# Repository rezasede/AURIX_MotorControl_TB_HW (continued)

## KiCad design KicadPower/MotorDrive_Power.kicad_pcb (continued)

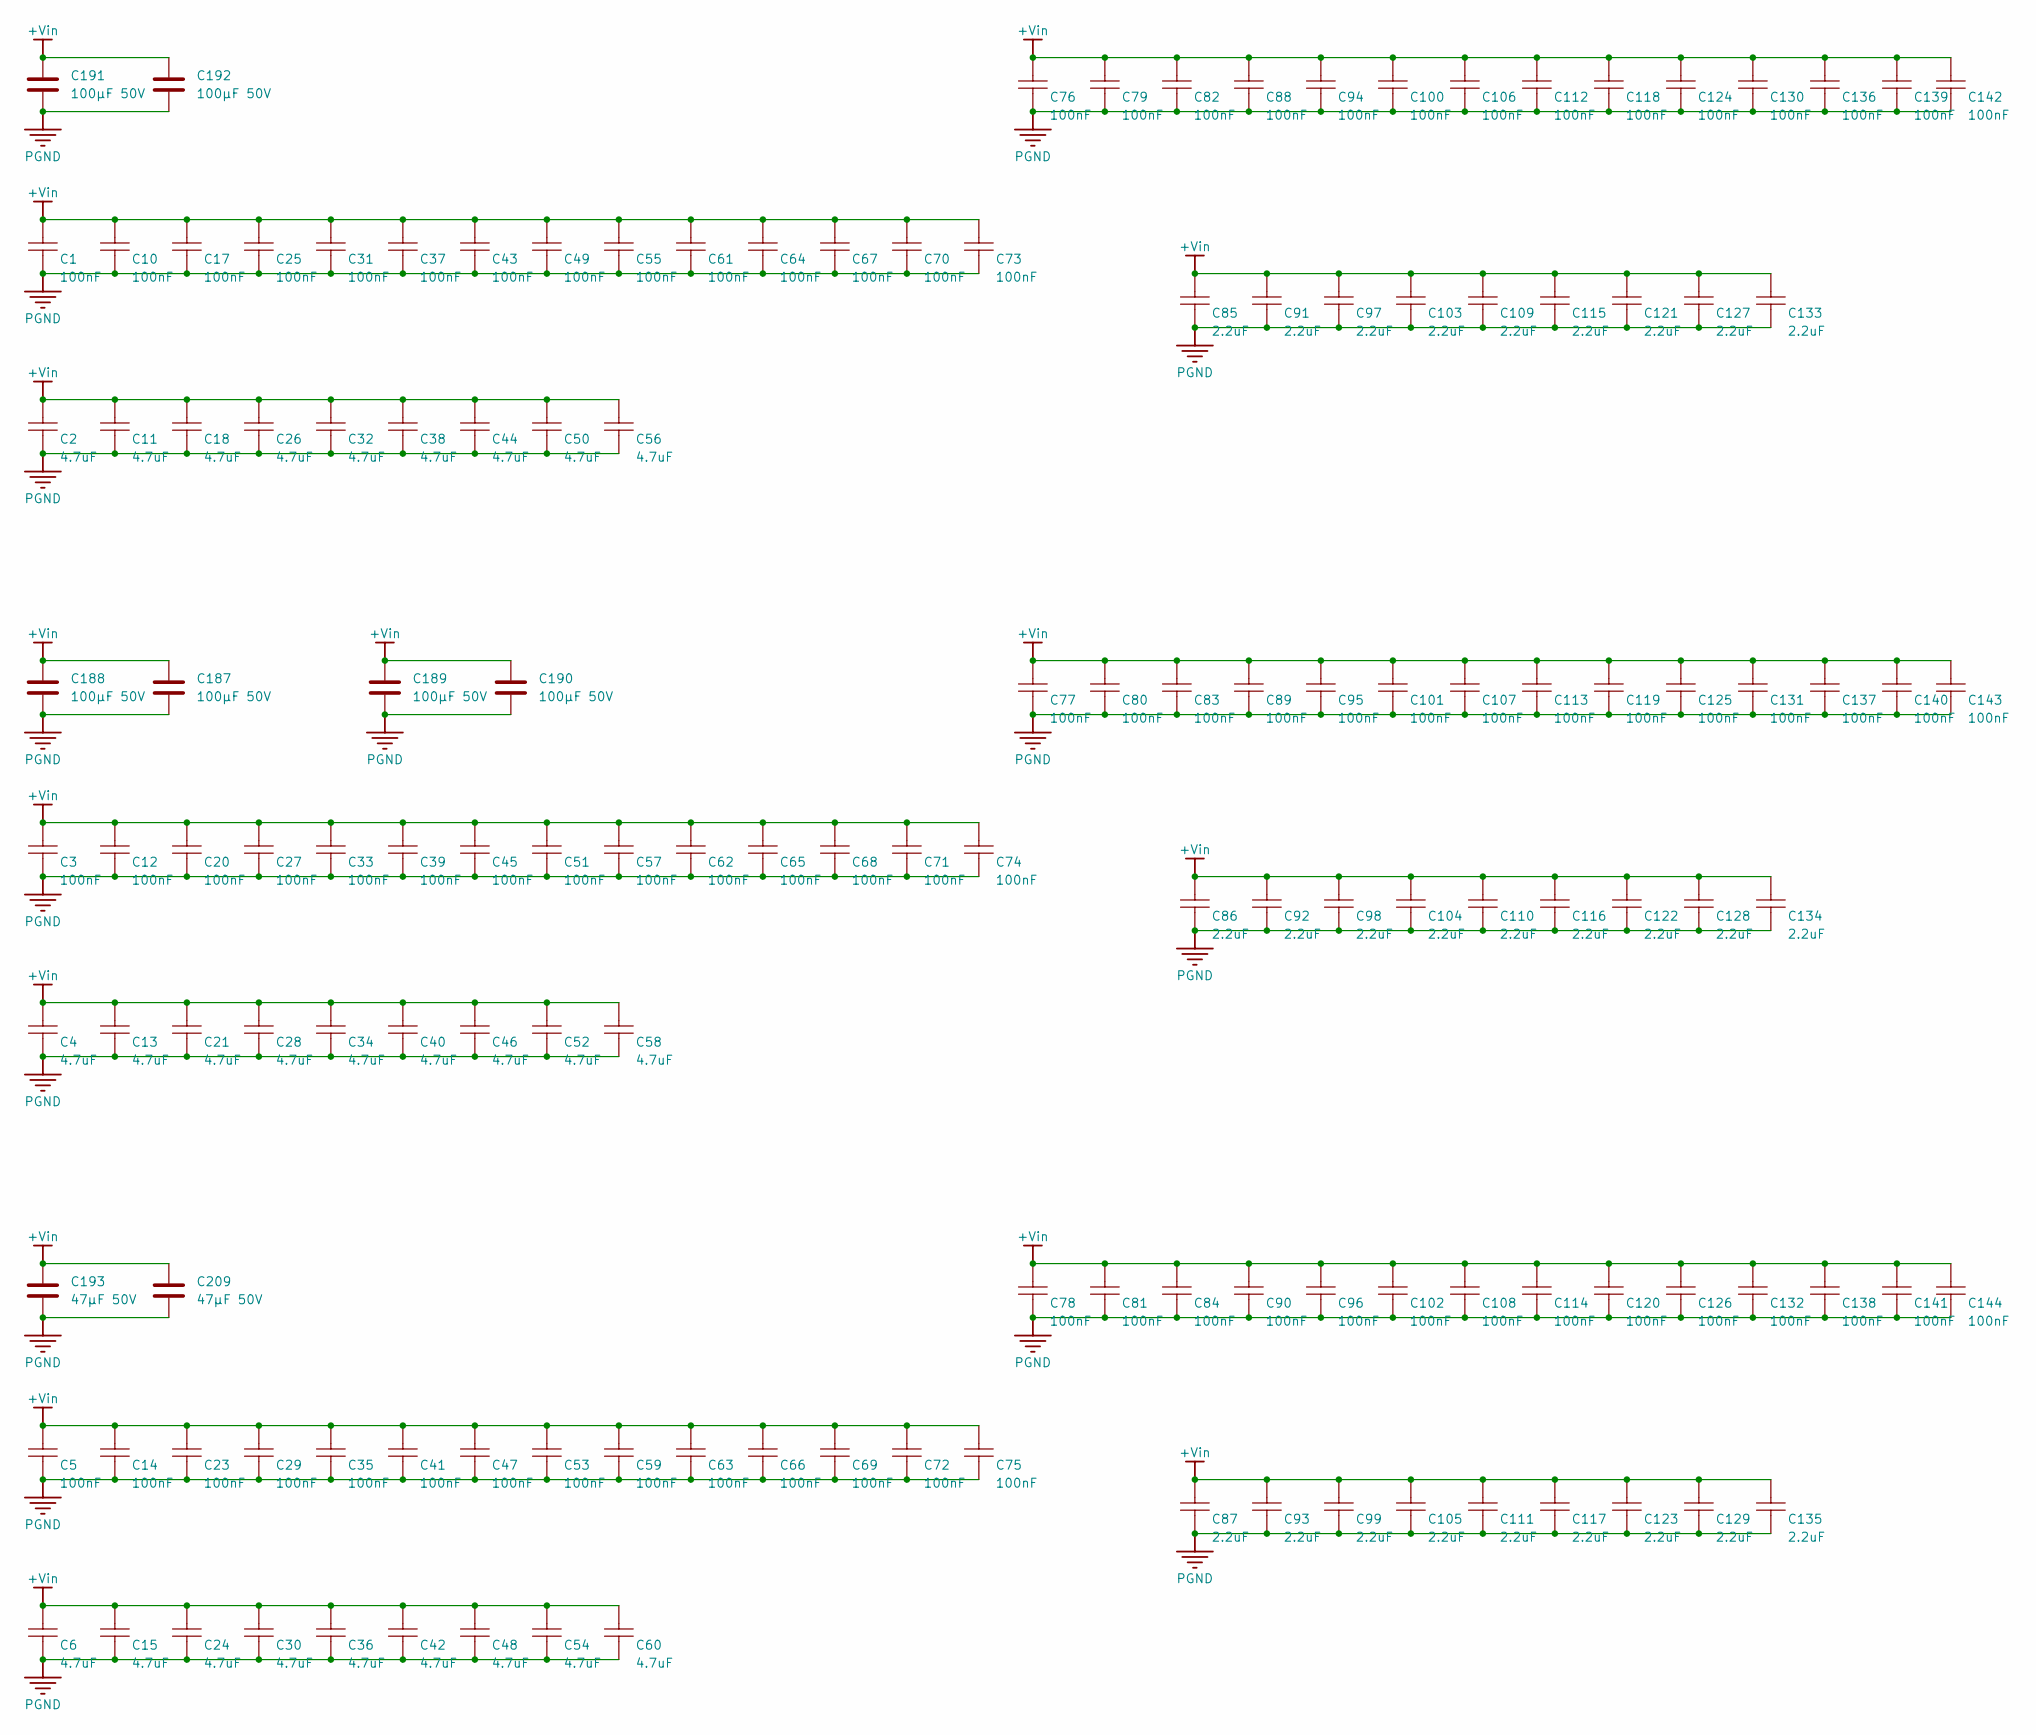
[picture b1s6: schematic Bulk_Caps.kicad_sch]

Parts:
C1, C3, C5, C10, C12, C14, C17, C20, C23, C25, C27, C29, C31, C33, C35, C37, C39, C41, C43, C45, C47, C49, C51, C53, C55, C57, C59, C61, C62, C63, C64, C65, C66, C67, C68, C69, C70, C71, C72, C73, C74, C75, C76, C77, C78, C79, C80, C81, C82, C83, C84, C88, C89, C90, C94, C95, C96, C100, C101, C102, C106, C107, C108, C112, C113, C114, C118, C119, C120, C124, C125, C126, C130, C131, C132, C136, C137, C138, C139, C140, C141, C142, C143, C144: Cap SMD; CAPC3216X100N
C2, C4, C6, C11, C13, C15, C18, C21, C24, C26, C28, C30, C32, C34, C36, C38, C40, C42, C44, C46, C48, C50, C52, C54, C56, C58, C60, C85, C86, C87, C91, C92, C93, C97, C98, C99, C103, C104, C105, C109, C110, C111, C115, C116, C117, C121, C122, C123, C127, C128, C129, C133, C134, C135: Cap SMD; CAPC3225X220N
C187, C188, C189, C190, C191, C192: 100µF 50V; C_Elec_8x10.2
C193, C209: 47µF 50V; C_Elec_6.3x7.7

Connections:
+Vin: C1.2, C2.2, C3.2, C4.2, C5.2, C6.2, C10.2, C11.2, C12.2, C13.2, C14.2, C15.2, C17.2, C18.2, C20.2, C21.2, C23.2, C24.2, C25.2, C26.2, C27.2, C28.2, C29.2, C30.2, C31.2, C32.2, C33.2, C34.2, C35.2, C36.2, C37.2, C38.2, C39.2, C40.2, C41.2, C42.2, C43.2, C44.2, C45.2, C46.2, C47.2, C48.2, C49.2, C50.2, C51.2, C52.2, C53.2, C54.2, C55.2, C56.2, C57.2, C58.2, C59.2, C60.2, C61.2, C62.2, C63.2, C64.2, C65.2, C66.2, C67.2, C68.2, C69.2, C70.2, C71.2, C72.2, C73.2, C74.2, C75.2, C76.2, C77.2, C78.2, C79.2, C80.2, C81.2, C82.2, C83.2, C84.2, C85.2, C86.2, C87.2, C88.2, C89.2, C90.2, C91.2, C92.2, C93.2, C94.2, C95.2, C96.2, C97.2, C98.2, C99.2, C100.2, C101.2, C102.2, C103.2, C104.2, C105.2, C106.2, C107.2, C108.2, C109.2, C110.2, C111.2, C112.2, C113.2, C114.2, C115.2, C116.2, C117.2, C118.2, C119.2, C120.2, C121.2, C122.2, C123.2, C124.2, C125.2, C126.2, C127.2, C128.2, C129.2, C130.2, C131.2, C132.2, C133.2, C134.2, C135.2, C136.2, C137.2, C138.2, C139.2, C140.2, C141.2, C142.2, C143.2, C144.2, C187.1, C188.1, C189.1, C190.1, C191.1, C192.1, C193.1, C209.1; also elsewhere on the board
PGND: C1.1, C2.1, C3.1, C4.1, C5.1, C6.1, C10.1, C11.1, C12.1, C13.1, C14.1, C15.1, C17.1, C18.1, C20.1, C21.1, C23.1, C24.1, C25.1, C26.1, C27.1, C28.1, C29.1, C30.1, C31.1, C32.1, C33.1, C34.1, C35.1, C36.1, C37.1, C38.1, C39.1, C40.1, C41.1, C42.1, C43.1, C44.1, C45.1, C46.1, C47.1, C48.1, C49.1, C50.1, C51.1, C52.1, C53.1, C54.1, C55.1, C56.1, C57.1, C58.1, C59.1, C60.1, C61.1, C62.1, C63.1, C64.1, C65.1, C66.1, C67.1, C68.1, C69.1, C70.1, C71.1, C72.1, C73.1, C74.1, C75.1, C76.1, C77.1, C78.1, C79.1, C80.1, C81.1, C82.1, C83.1, C84.1, C85.1, C86.1, C87.1, C88.1, C89.1, C90.1, C91.1, C92.1, C93.1, C94.1, C95.1, C96.1, C97.1, C98.1, C99.1, C100.1, C101.1, C102.1, C103.1, C104.1, C105.1, C106.1, C107.1, C108.1, C109.1, C110.1, C111.1, C112.1, C113.1, C114.1, C115.1, C116.1, C117.1, C118.1, C119.1, C120.1, C121.1, C122.1, C123.1, C124.1, C125.1, C126.1, C127.1, C128.1, C129.1, C130.1, C131.1, C132.1, C133.1, C134.1, C135.1, C136.1, C137.1, C138.1, C139.1, C140.1, C141.1, C142.1, C143.1, C144.1, C187.2, C188.2, C189.2, C190.2, C191.2, C192.2, C193.2, C209.2; also elsewhere on the board

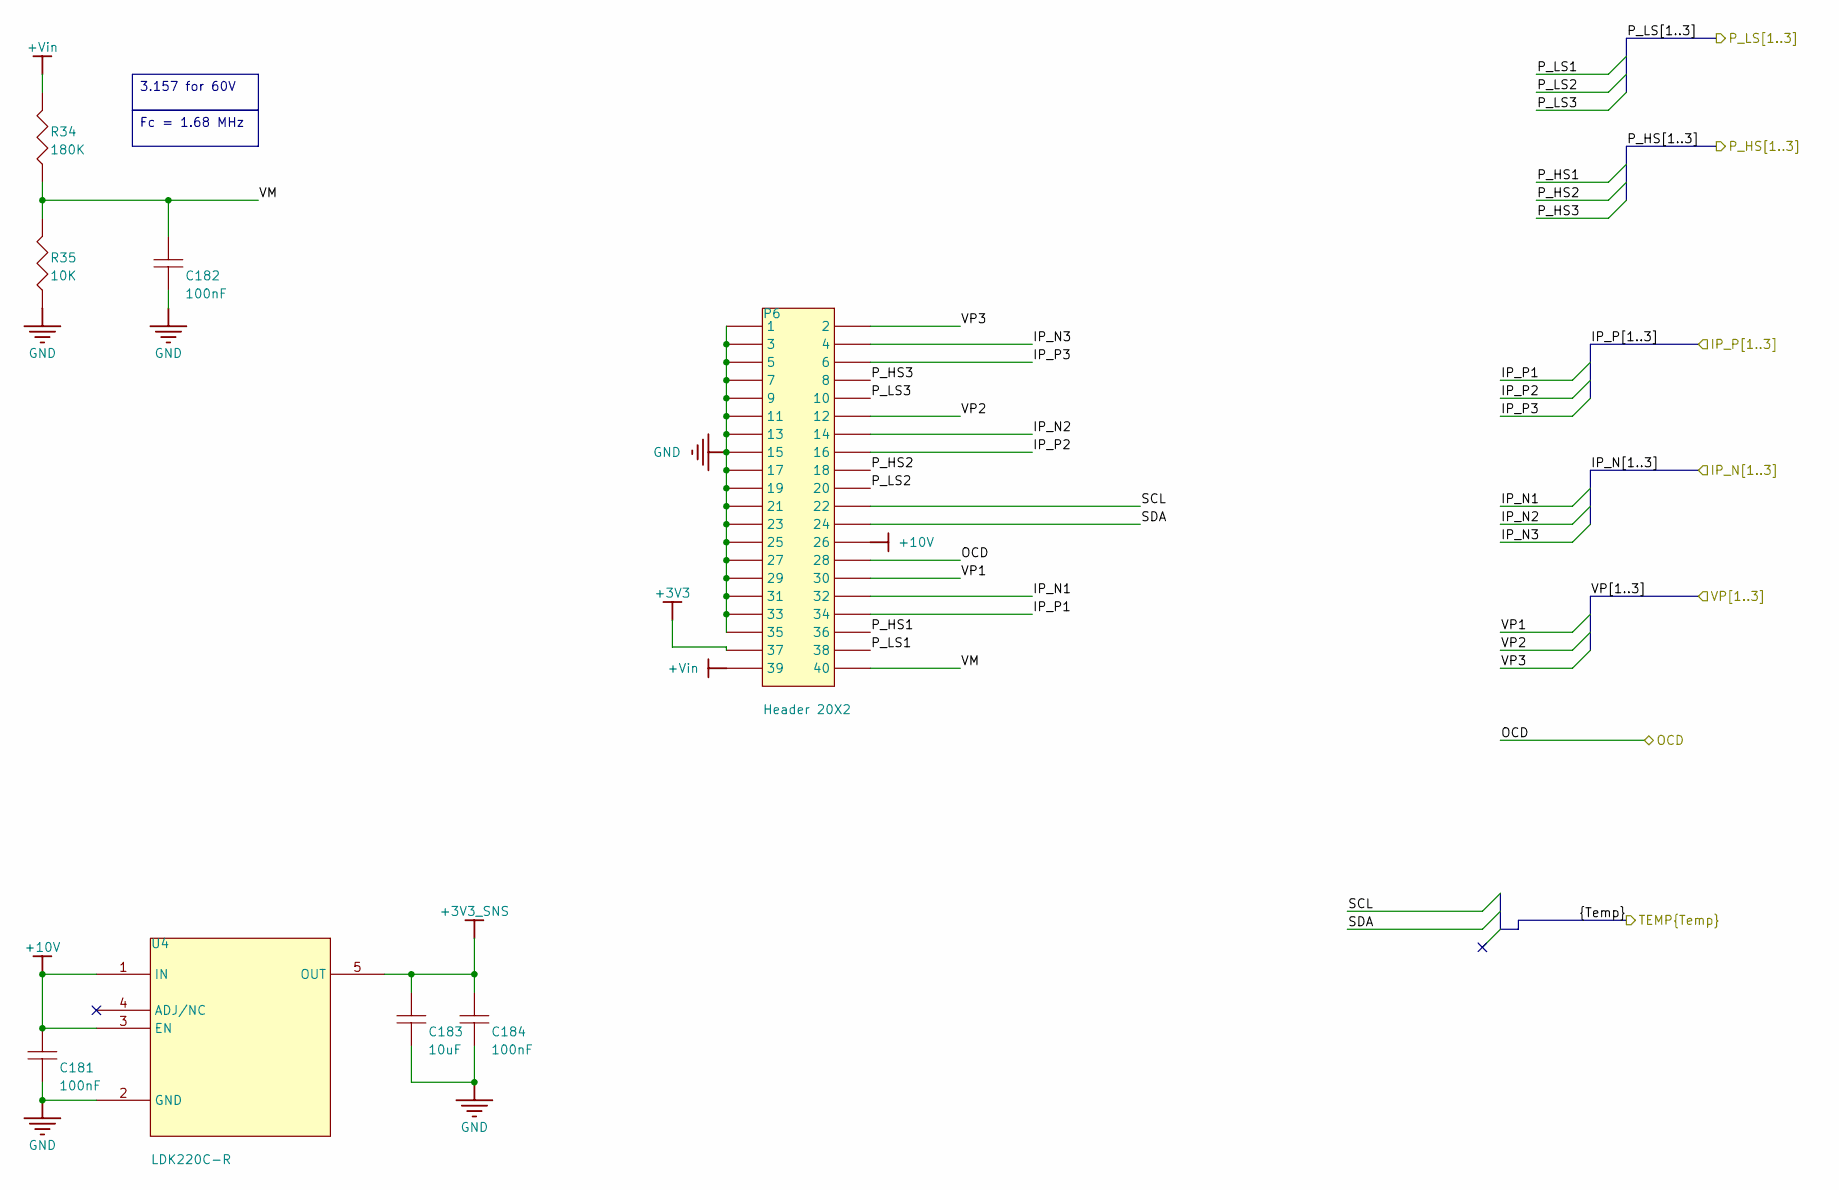
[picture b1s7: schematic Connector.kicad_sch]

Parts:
C181, C182, C183, C184: Cap SMD; CAPC1608X90N
P6: Header 20X2; HDR2X20-MD
R34, R35: Res SMD; RESC1608X55N
U4: LDK220C-R; SOT_220M-R_STM; MANUFACTURER_PART_NUMBER LDK220C-R

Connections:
+3V3: P6.37; also elsewhere on the board
+3V3_SNS: C183.2, C184.2, U4.5 (OUT); also elsewhere on the board
+10V: C181.2, P6.26, U4.1 (IN), U4.3 (EN); also elsewhere on the board
+Vin: P6.39, R34.2; also elsewhere on the board
/IP_N1: P6.32; also elsewhere on the board
/IP_N2: P6.14; also elsewhere on the board
/IP_N3: P6.4; also elsewhere on the board
/IP_P1: P6.34; also elsewhere on the board
/IP_P2: P6.16; also elsewhere on the board
/IP_P3: P6.6; also elsewhere on the board
/OCD: P6.28; also elsewhere on the board
/P_HS1: P6.36; also elsewhere on the board
/P_HS2: P6.18; also elsewhere on the board
/P_HS3: P6.8; also elsewhere on the board
/P_LS1: P6.38; also elsewhere on the board
/P_LS2: P6.20; also elsewhere on the board
/P_LS3: P6.10; also elsewhere on the board
/U_Connector/SCL: P6.22; also elsewhere on the board
/U_Connector/SDA: P6.24; also elsewhere on the board
/U_Connector/VM: C182.2, P6.40, R34.1, R35.2
/VP1: P6.30; also elsewhere on the board
/VP2: P6.12; also elsewhere on the board
/VP3: P6.2; also elsewhere on the board
GND: C181.1, C182.1, C183.1, C184.1, P6.1, P6.3, P6.5, P6.7, P6.9, P6.11, P6.13, P6.15, P6.17, P6.19, P6.21, P6.23, P6.25, P6.27, P6.29, P6.31, P6.33, P6.35, R35.1, U4.2 (GND); also elsewhere on the board

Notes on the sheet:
3.157 for 60V
Fc = 1.68 MHz

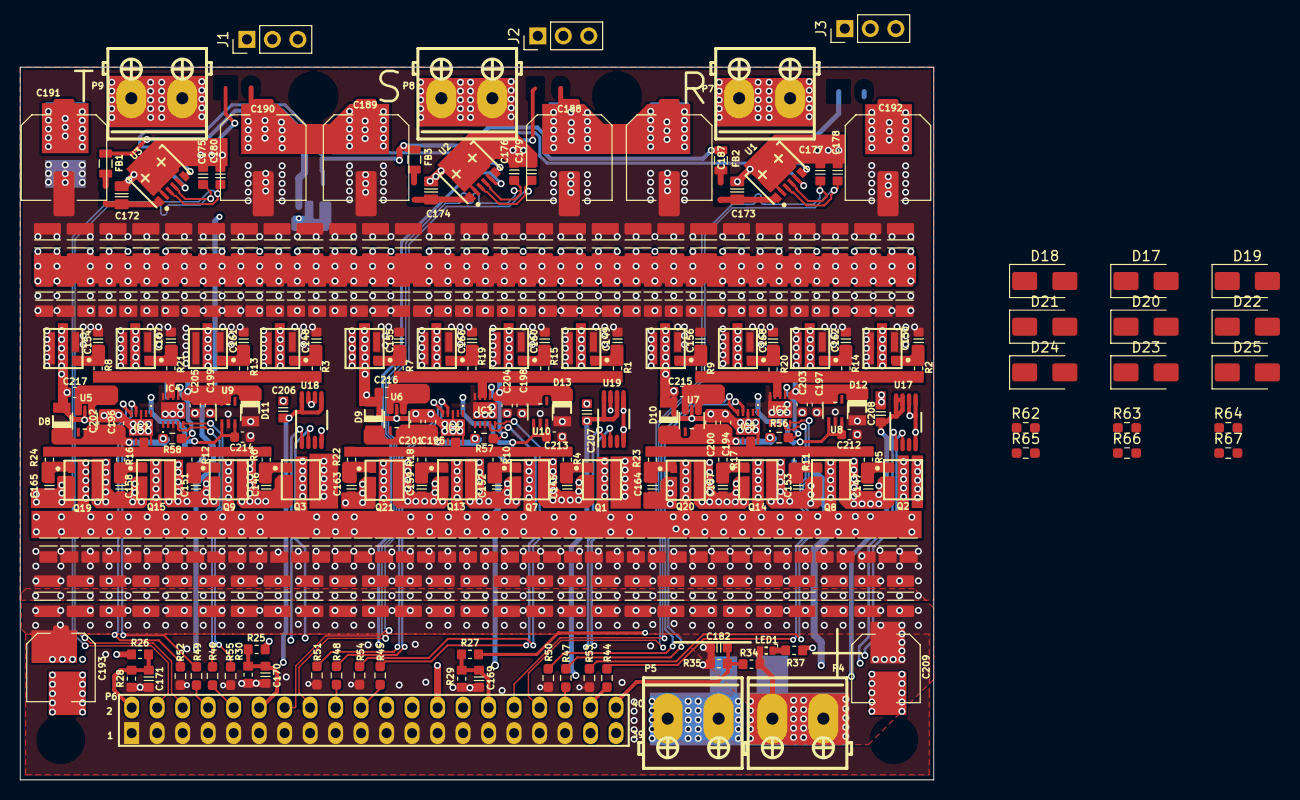
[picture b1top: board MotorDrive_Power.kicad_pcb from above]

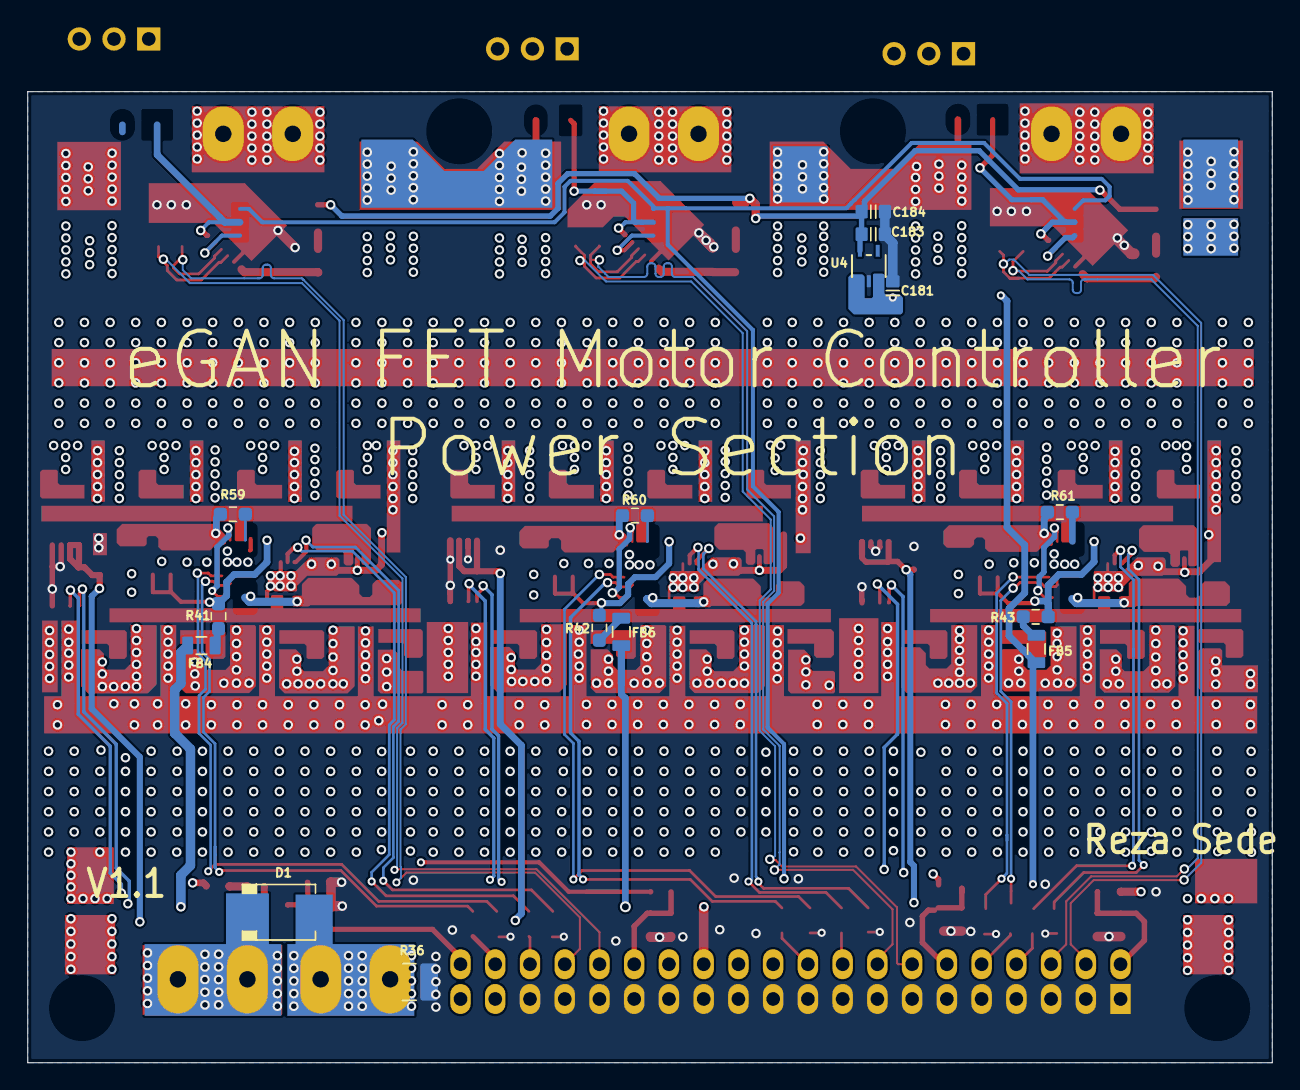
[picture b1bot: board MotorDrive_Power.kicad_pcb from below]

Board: 6 copper layers, 91.0 x 71.0 mm, 343 parts (15 on the bottom side), 104 nets.

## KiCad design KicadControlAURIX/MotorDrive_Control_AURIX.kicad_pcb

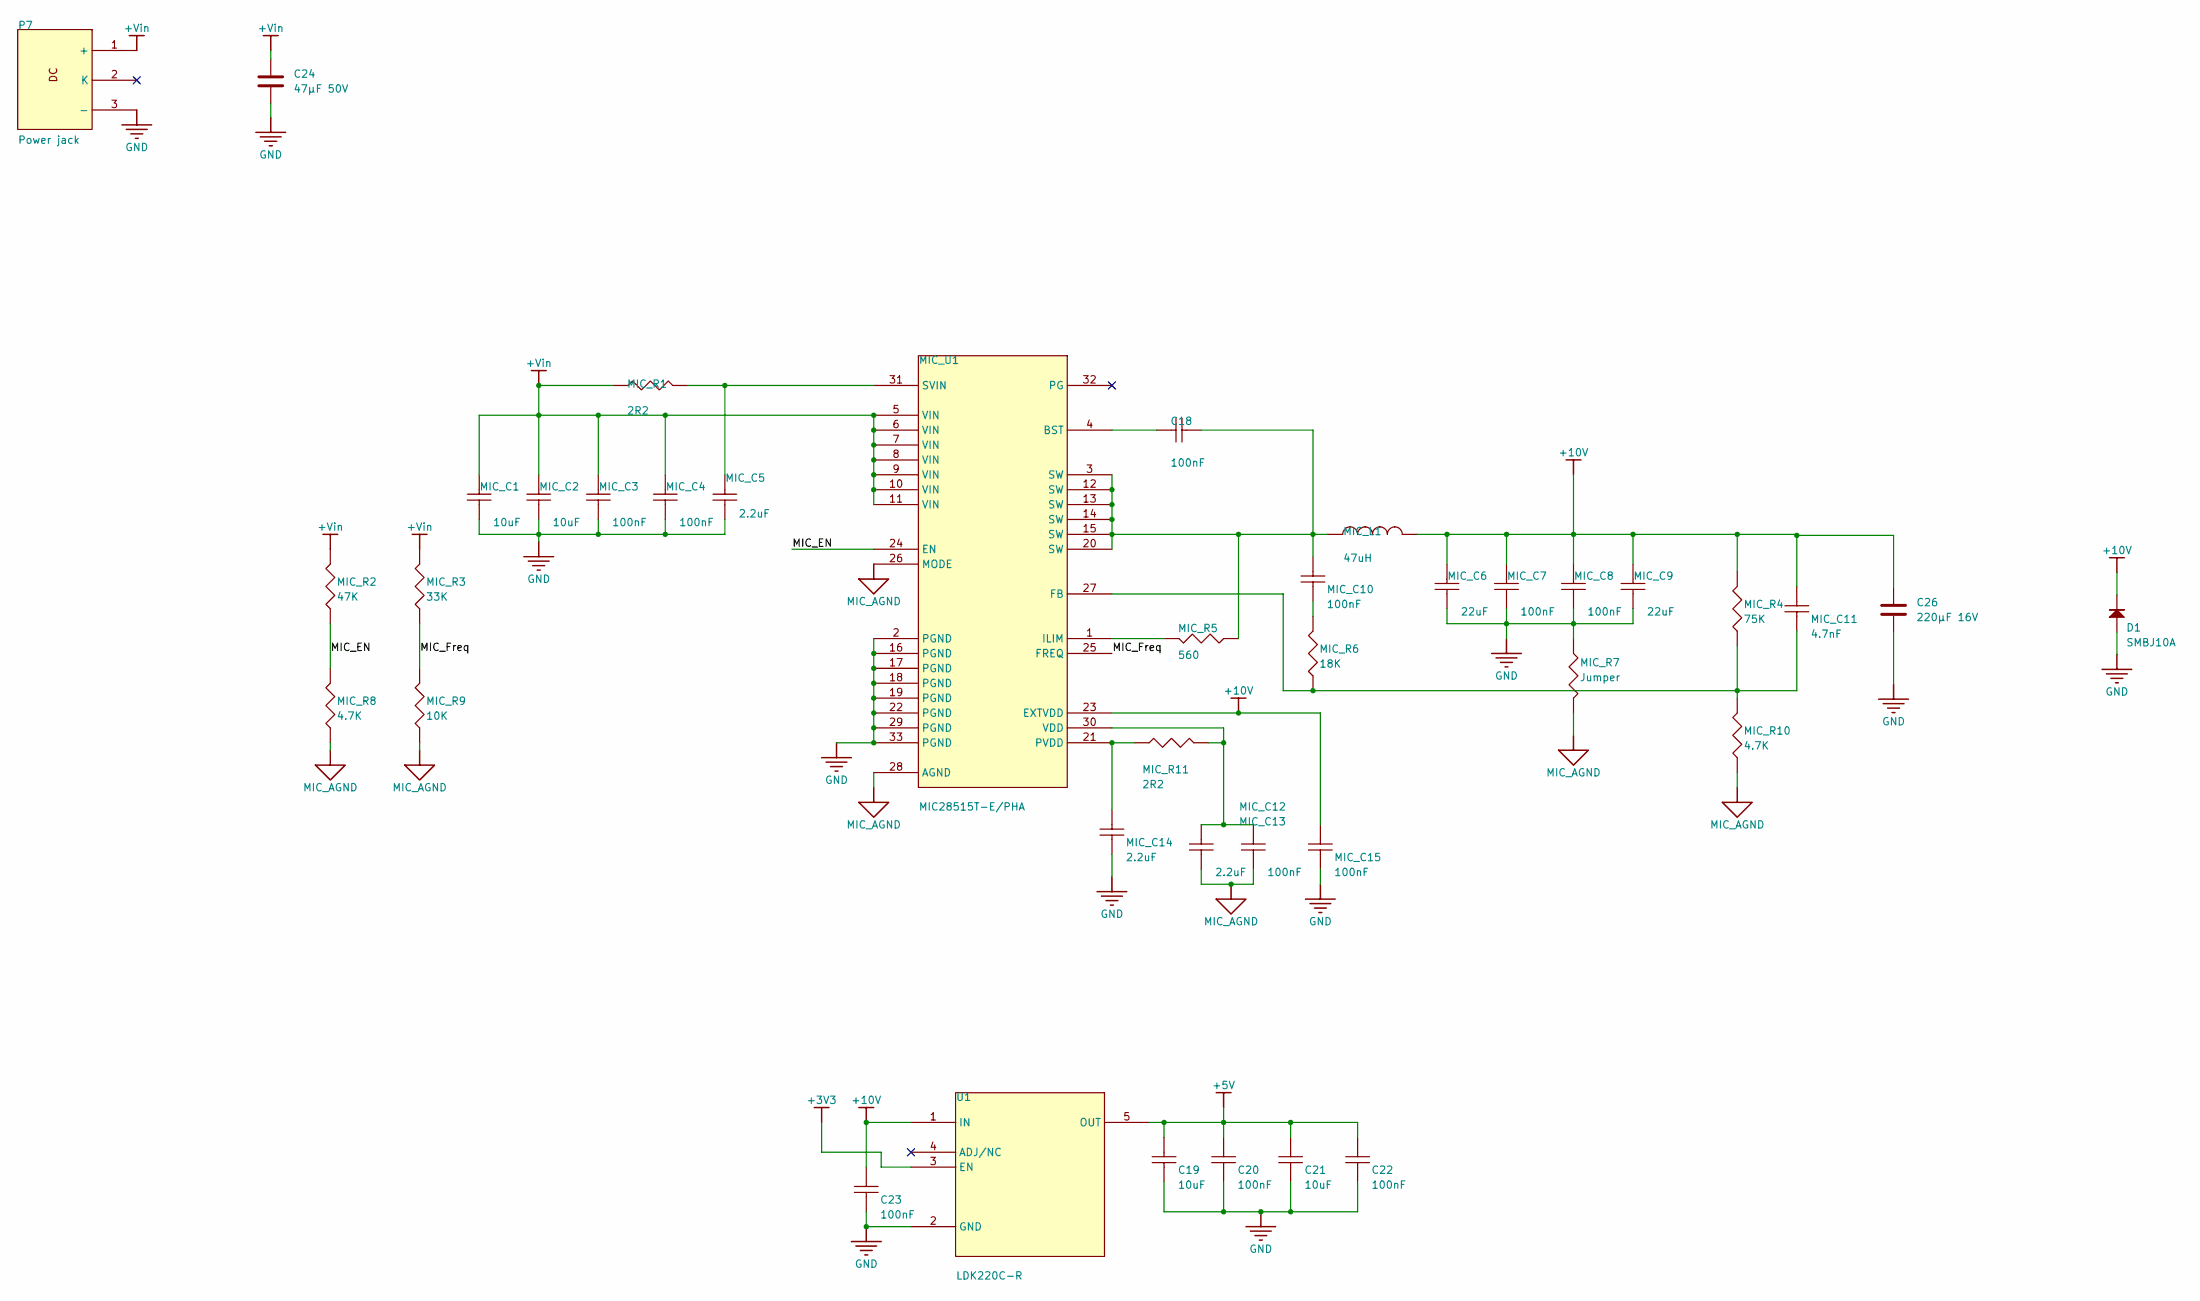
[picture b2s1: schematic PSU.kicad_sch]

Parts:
C18, C20, C22, C23: Cap SMD; CAPC1608X90N
C19, C21: Cap SMD; CAPC2012X135N
C24: 47µF 50V; C_Elec_6.3x7.7
C26: 220µF 16V; C_Elec_6.3x7.7
D1: SMBJ10A; DO-214AA
MIC_C1, MIC_C2, MIC_C5, MIC_C6, MIC_C9, MIC_C12, MIC_C14: Cap SMD; CAPC3216X100N
MIC_C3, MIC_C4, MIC_C13, MIC_C15: Cap SMD; CAPC2012X135N
MIC_C7, MIC_C8, MIC_C10, MIC_C11: Cap SMD; CAPC1608X90N
MIC_L1: Inductor; SCD503T-101K-N
MIC_R1, MIC_R2, MIC_R3, MIC_R4, MIC_R5, MIC_R6, MIC_R7, MIC_R8, MIC_R9, MIC_R10, MIC_R11: Res SMD; RESC1608X55N
MIC_U1: MIC28515T-E/PHA; VQFN32_PHA_MCH-M
P7: Power jack; power jaCK
U1: LDK220C-R; SOT_220M-R_STM; MANUFACTURER_PART_NUMBER LDK220C-R

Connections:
+3V3: U1.3 (EN); also elsewhere on the board
+5V: C19.2, C20.2, C21.2, C22.2, U1.5 (OUT); also elsewhere on the board
+10V: C23.2, C26.1, D1.K (2), MIC_C6.2, MIC_C7.2, MIC_C8.2, MIC_C9.2, MIC_C11.2, MIC_C15.2, MIC_L1.2, MIC_R4.2, MIC_U1.23 (EXTVDD), U1.1 (IN); also elsewhere on the board
+Vin: C24.1, MIC_C1.2, MIC_C2.2, MIC_C3.2, MIC_C4.2, MIC_R1.1, MIC_R2.2, MIC_R3.2, MIC_U1.5 (VIN), MIC_U1.6 (VIN), MIC_U1.7 (VIN), MIC_U1.8 (VIN), MIC_U1.9 (VIN), MIC_U1.10 (VIN), MIC_U1.11 (VIN), P7.1 (+); also elsewhere on the board
/U_PSU/MIC_EN: MIC_R2.1, MIC_R8.2, MIC_U1.24 (EN)
/U_PSU/MIC_Freq: MIC_R3.1, MIC_R9.2, MIC_U1.25 (FREQ)
GND: C19.1, C20.1, C21.1, C22.1, C23.1, C24.2, C26.2, D1.A (1), MIC_C1.1, MIC_C2.1, MIC_C3.1, MIC_C4.1, MIC_C5.2, MIC_C6.1, MIC_C7.1, MIC_C8.1, MIC_C9.1, MIC_C14.1, MIC_C15.1, MIC_R7.1, MIC_U1.2 (PGND), MIC_U1.16 (PGND), MIC_U1.17 (PGND), MIC_U1.18 (PGND), MIC_U1.19 (PGND), MIC_U1.22 (PGND), MIC_U1.29 (PGND), MIC_U1.33 (PGND), P7.3 (-), U1.2 (GND); also elsewhere on the board
MIC_AGND: MIC_C12.1, MIC_C13.1, MIC_R7.2, MIC_R8.1, MIC_R9.1, MIC_R10.1, MIC_U1.26 (MODE), MIC_U1.28 (AGND)
unnamed: C18.2, MIC_C10.2, MIC_L1.1, MIC_R5.1, MIC_U1.3 (SW), MIC_U1.12 (SW), MIC_U1.13 (SW), MIC_U1.14 (SW), MIC_U1.15 (SW), MIC_U1.20 (SW)
unnamed: MIC_C10.1, MIC_R6.2
unnamed: C18.1, MIC_U1.4 (BST)
unnamed: MIC_C11.1, MIC_R4.1, MIC_R6.1, MIC_R10.2, MIC_U1.27 (FB)
unnamed: MIC_R5.2, MIC_U1.1 (ILIM)
unnamed: MIC_C14.2, MIC_R11.1, MIC_U1.21 (PVDD)
unnamed: MIC_C5.1, MIC_R1.2, MIC_U1.31 (SVIN)
unnamed: MIC_C12.2, MIC_C13.2, MIC_R11.2, MIC_U1.30 (VDD)

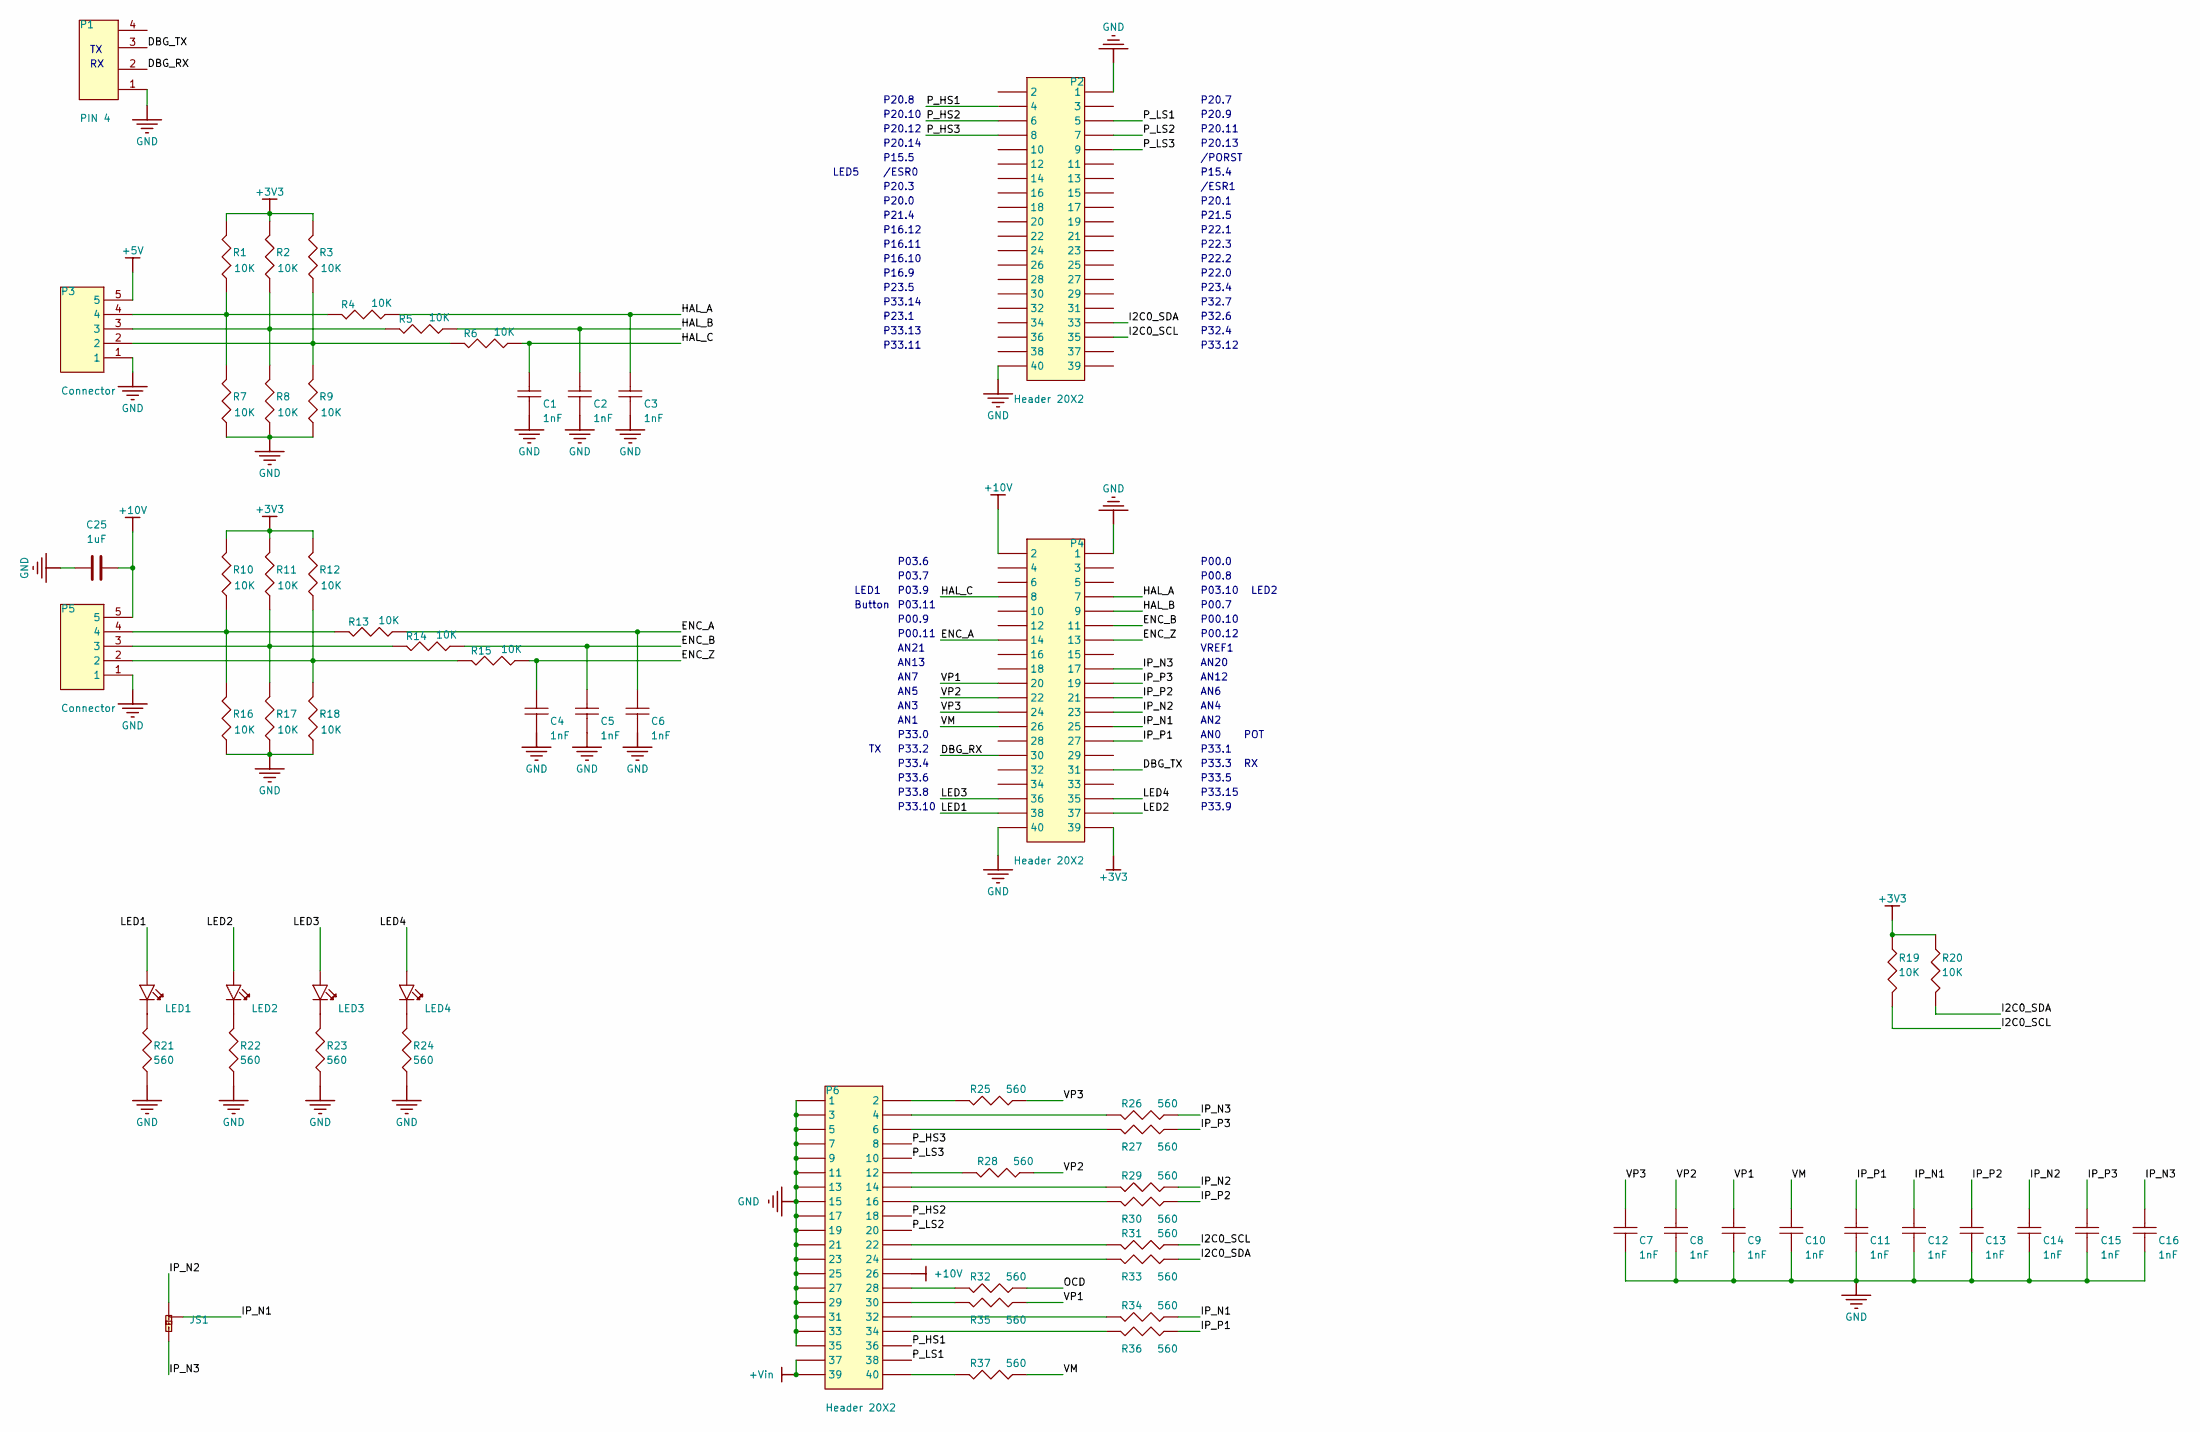
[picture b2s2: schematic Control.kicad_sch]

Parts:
C1, C2, C3, C4, C5, C6, C7, C8, C9, C10, C11, C12, C13, C14, C15, C16: Cap SMD; CAPC1608X90N
C25: 1uF; C_0805_2012Metric_Pad1.18x1.45mm_HandSolder
JS1: JumperSMD 3Pin; JumperSMD 3Pin - UltraSmall
LED1, LED2, LED3, LED4: LED; LED0603
P1: PIN 4; PIN F4
P2, P4: Header 20X2; HDR2X20-MU
P3, P5: Connector; PH Connector 5Pin
P6: Header 20X2; HDR2X20-MD
R1, R2, R3, R4, R5, R6, R7, R8, R9, R10, R11, R12, R13, R14, R15, R16, R17, R18, R19, R20, R21, R22, R23, R24, R25, R26, R27, R28, R29, R30, R31, R32, R33, R34, R35, R36, R37: Res SMD; RESC1608X55N

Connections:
+3V3: P4.39, R1.2, R2.2, R3.2, R10.2, R11.2, R12.2, R19.1, R20.1; also elsewhere on the board
+5V: P3.5; also elsewhere on the board
+10V: C25.2, P4.2, P5.5, P6.26; also elsewhere on the board
+Vin: P6.37, P6.39; also elsewhere on the board
/U_Control/DBG_RX: P1.2, P4.30
/U_Control/DBG_TX: P1.3, P4.31
/U_Control/ENC_A: C6.2, P4.14, R13.1
/U_Control/ENC_B: C5.2, P4.11, R14.1
/U_Control/ENC_Z: C4.2, P4.13, R15.1
/U_Control/HAL_A: C3.2, P4.7, R4.1
/U_Control/HAL_B: C2.2, P4.9, R5.1
/U_Control/HAL_C: C1.2, P4.8, R6.1
/U_Control/I2C0_SCL: P2.35, R19.2, R31.1
/U_Control/I2C0_SDA: P2.33, R20.2, R33.1
/U_Control/IP_N1: C12.2, JS1.2, P4.25, R34.1
/U_Control/IP_N2: C14.2, JS1.1, P4.23, R29.1
/U_Control/IP_N3: C16.2, JS1.3, P4.17, R26.1
/U_Control/IP_P1: C11.2, P4.27, R36.1
/U_Control/IP_P2: C13.2, P4.21, R30.1
/U_Control/IP_P3: C15.2, P4.19, R27.1
/U_Control/LED1: LED1.1 (A), P4.38
/U_Control/LED2: LED2.1 (A), P4.37
/U_Control/LED3: LED3.1 (A), P4.36
/U_Control/LED4: LED4.1 (A), P4.35
/U_Control/OCD: R32.1
/U_Control/P_HS1: P2.4, P6.36
/U_Control/P_HS2: P2.6, P6.18
/U_Control/P_HS3: P2.8, P6.8
/U_Control/P_LS1: P2.5, P6.38
/U_Control/P_LS2: P2.7, P6.20
/U_Control/P_LS3: P2.9, P6.10
/U_Control/VM: C10.2, P4.26, R37.1
/U_Control/VP1: C9.2, P4.20, R35.1
/U_Control/VP2: C8.2, P4.22, R28.1
/U_Control/VP3: C7.2, P4.24, R25.1
GND: C1.1, C2.1, C3.1, C4.1, C5.1, C6.1, C7.1, C8.1, C9.1, C10.1, C11.1, C12.1, C13.1, C14.1, C15.1, C16.1, C25.1, P1.1, P2.1, P2.40, P3.1, P4.1, P4.40, P5.1, P6.1, P6.3, P6.5, P6.7, P6.9, P6.11, P6.13, P6.15, P6.17, P6.19, P6.21, P6.23, P6.25, P6.27, P6.29, P6.31, P6.33, P6.35, R7.1, R8.1, R9.1, R16.1, R17.1, R18.1, R21.1, R22.1, R23.1, R24.1; also elsewhere on the board
unnamed: LED1.2 (K), R21.2
unnamed: LED2.2 (K), R22.2
unnamed: LED3.2 (K), R23.2
unnamed: LED4.2 (K), R24.2
unnamed: P3.2, R3.1, R6.2, R9.2
unnamed: P3.3, R2.1, R5.2, R8.2
unnamed: P3.4, R1.1, R4.2, R7.2
unnamed: P5.2, R12.1, R15.2, R18.2
unnamed: P5.3, R11.1, R14.2, R17.2
unnamed: P5.4, R10.1, R13.2, R16.2
unnamed: P6.2, R25.2
unnamed: P6.4, R26.2
unnamed: P6.6, R27.2
unnamed: P6.12, R28.2
unnamed: P6.14, R29.2
unnamed: P6.16, R30.2
unnamed: P6.22, R31.2
unnamed: P6.24, R33.2
unnamed: P6.28, R32.2
unnamed: P6.30, R35.2
unnamed: P6.32, R34.2
unnamed: P6.34, R36.2
unnamed: P6.40, R37.2

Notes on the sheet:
P00.11
AN0
P20.0
/PORST
LED5
P00.9
P15.4
P16.10
P16.11
LED2
P33.9
AN6
P33.2
P20.9
AN13
P33.12
P20.11
P20.12
P23.1
P33.1
P22.2
P00.10
Button
P00.7
P33.14
P16.9
AN1
P21.5
P23.4
VREF1
P33.0
P33.8
P33.15
P03.10
P00.12
AN21
P03.6
POT
P00.0
AN20

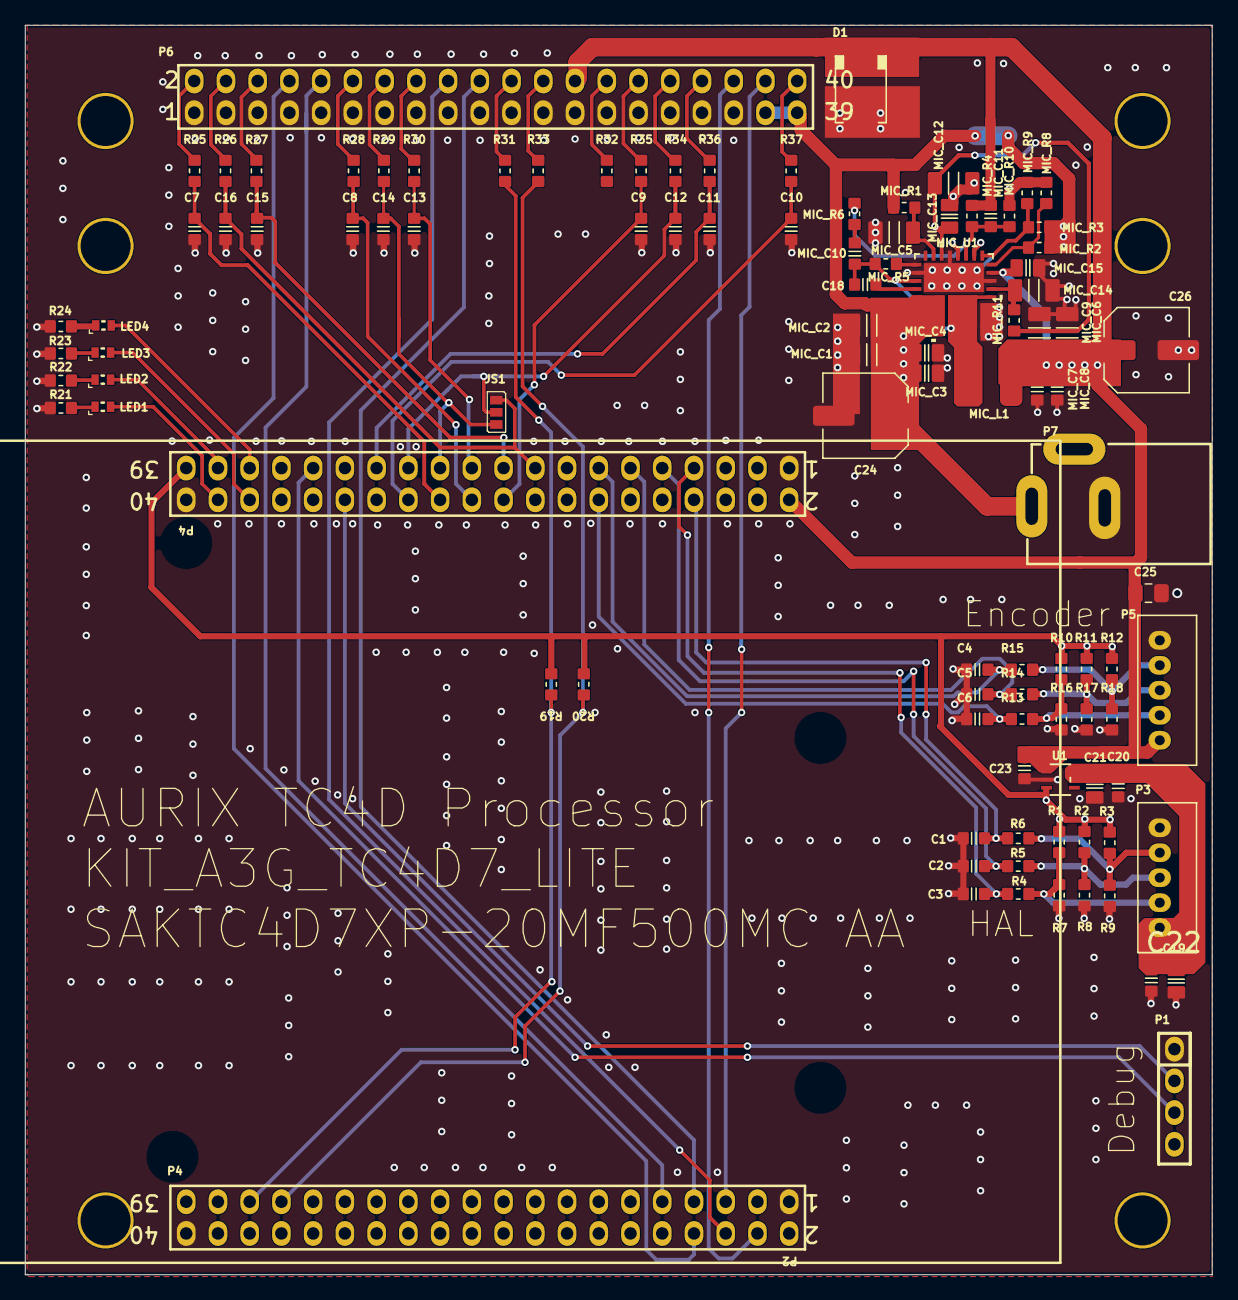
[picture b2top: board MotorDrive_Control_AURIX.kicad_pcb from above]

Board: 2 copper layers, 95.0 x 100.0 mm, 104 parts (1 on the bottom side), 69 nets.

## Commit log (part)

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2026-04-02 successful migration and fixing in kicad
2026-04-02 minor changes
2026-04-03 new G serie of Driver modifed and finished
2026-04-04 changed
2026-04-05 Sent for Manufacturing V1.0
2026-06-22 added PDF
